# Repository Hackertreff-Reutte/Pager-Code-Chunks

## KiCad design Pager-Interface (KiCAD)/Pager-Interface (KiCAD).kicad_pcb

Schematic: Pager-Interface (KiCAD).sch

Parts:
H1, H2, H3: M3; MountingHole_3.2mm_M3_DIN965_Pad_TopBottom
J1: VSPI; PinHeader_1x06_P2.54mm_Vertical
J2: HSPI; PinHeader_1x06_P2.54mm_Vertical
J3: Serial; PinHeader_1x04_P2.54mm_Vertical
J4: Serial2; PinHeader_1x04_P2.54mm_Vertical
J5: SMA ANT; SMA_Molex_73251-2120_EdgeMount_Horizontal
J6: Ext Power; PinHeader_1x02_P2.54mm_Vertical
J7: Debug SI4432; PinHeader_1x05_P2.54mm_Vertical
J8: Power; PinHeader_1x02_P2.54mm_Vertical
U1: ESP32_NodeMCU
U2: SI4432-Module

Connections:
+3V3: J1.1, J2.1, J3.1, J4.1, J8.1, U1.15, U2.5
/HSPI_CLK: J2.4, U1.20
/HSPI_CS: J2.5, U1.13
/HSPI_MISO: J2.3, U1.19
/HSPI_MOSI: J2.2, U1.18
/RSSI: J7.3, U1.25, U2.4
/RX0: J3.3, U1.4
/RX2: J4.3, U1.10
/RX_Clock: J7.2, U1.26, U2.3
/RX_Data: J7.1, U1.27, U2.2
/SDN: U1.11, U2.11
/TX0: J3.2, U1.3
/TX2: J4.2, U1.9
/VIN: J6.1, U1.16
/VSPI_CLK: J1.4, U1.7, U2.8
/VSPI_CS: J1.5, U1.8, U2.9
/VSPI_MISO: J1.3, U1.6, U2.6
/VSPI_MOSI: J1.2, U1.1, U2.7
/nIRQ: J7.4, U1.12, U2.10
GND: H1.1, H2.1, H3.1, J1.6, J2.6, J3.4, J4.4, J5.2 (Ext), J6.2, J7.5, J8.2, U1.14, U1.17, U2.1, U2.12, U2.14
unnamed: J5.1 (In), U2.13

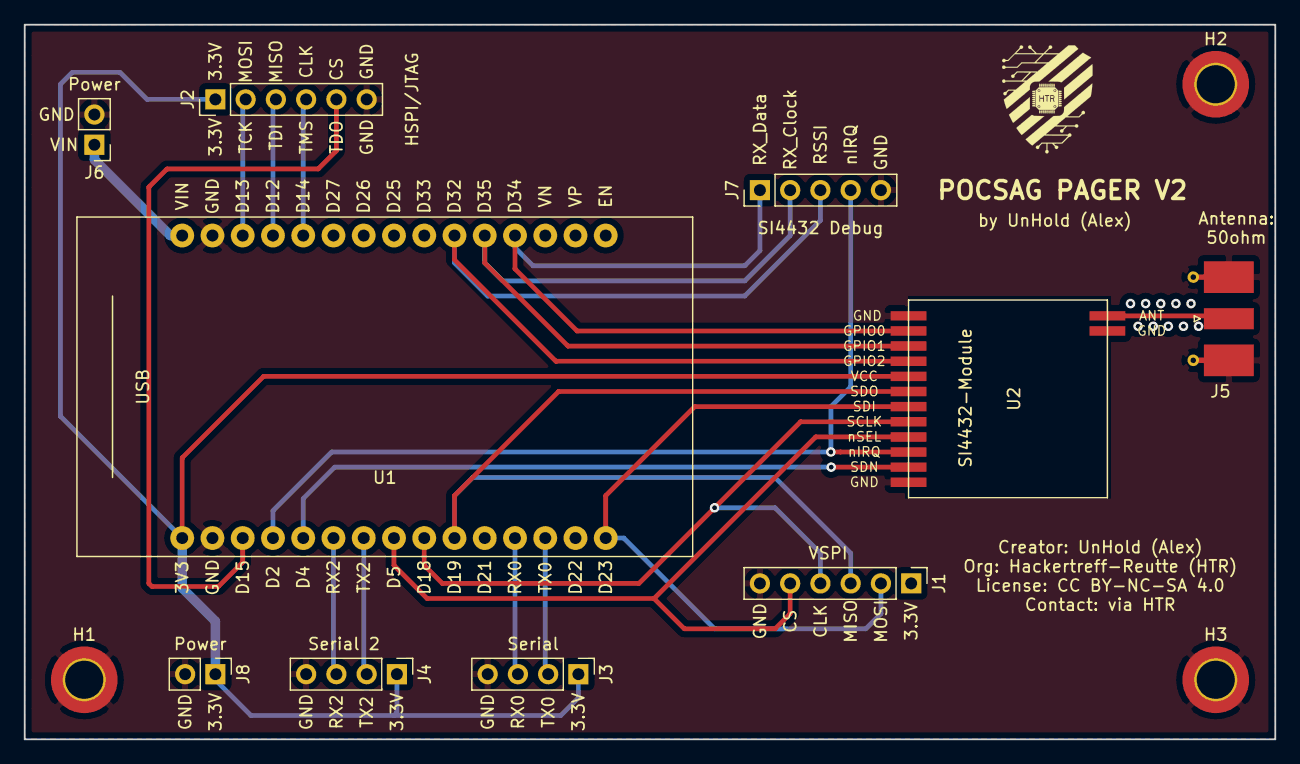
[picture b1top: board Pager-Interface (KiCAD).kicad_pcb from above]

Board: 2 copper layers, 105.0 x 60.0 mm, 13 parts (0 on the bottom side), 21 nets.

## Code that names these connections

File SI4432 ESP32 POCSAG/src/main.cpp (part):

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#include <math.h>
#include <signal.h>

#define HSPI_MISO   12
#define HSPI_MOSI   13
#define HSPI_SCLK   14
#define HSPI_SS     15

#define SDN 16


#define BUFFER_SIZE 1000
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double MODEM_DEVIATION = DEVIATION * 4;

#define INTERRUPT_PIN 5
#define RX_CLOCK_PIN 18
#define RX_DATA_PIN 19
#define RSSI_PIN 21

#define RSSI_RELATIVE_NO_SIGNAL_INDICATOR 0.9

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    return;
  }

  if(digitalRead(RX_CLOCK_PIN) == LOW){
    return;
  }

  tx_buf[si4432_count] |= digitalRead(RX_DATA_PIN) << (7 - si4432_count_shift);

  si4432_count_shift = (si4432_count_shift + 1) % 8;

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
      si4432_count = 0;
      tx_buf[0] = 0;
      attachInterrupt(RX_CLOCK_PIN, si4432_rx_clock_isr, RISING);
      attachInterrupt(RSSI_PIN, si4432_rssi_isr, FALLING);
    }
}

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  setModulationDataSource(SOURCE_DIRECT_SPI);
  setDirectClockSource(NO_TX_DATA_CLK);

  pinMode(RX_CLOCK_PIN, INPUT);
  pinMode(RX_DATA_PIN, INPUT);
  pinMode(INTERRUPT_PIN, INPUT);
  pinMode(RSSI_PIN, INPUT);

  write(0x06, 0b01000000); // disable interrupt (only Preamble interrupt)

  enableRXOutputPins();
  write(0x0D, 0b11100); //RSSI clear channel indicator on GPIO 2

  //register interrupt
  attachInterrupt(INTERRUPT_PIN, si4432_ISR, FALLING);
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  
  //this reset is important because otherwise spi might not be working on the
  //si4432
  pinMode(SDN, OUTPUT);
  digitalWrite(SDN, HIGH);
  delay(500);
  digitalWrite(SDN, LOW);
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  if(si4432_active_receive >= 1){
    if(si4432_active_receive >= 2){
      si4432_active_receive = 0;
      detachInterrupt(RX_CLOCK_PIN);
      detachInterrupt(RSSI_PIN);
      setIDLEMode();

      //send the data
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
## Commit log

2019-11-05 add bch code generator (proof of concept)
2019-11-06 Java program that can generate digitale audio signale (used for the generation of pocsag signals for a radio to transmit)
2019-11-07 added single bit and dual bit code correction
2021-02-16 added code chunks to help with the programming and debugging of the si4432
2021-02-16 renamed file to full name
2021-02-16 added esp32 example code on how to use the si4432 chip for pocsag RX and TX
2021-02-16 removed some duplicated files and fixed the name of a file
2021-02-18 added pocsag RX and TX support via UART
2021-02-20 added basic encoder and decoder + uart conrtol of si4432 + esp32
2021-02-20 fixed transmission size (was too small)
2021-02-21 added python file to fully control the esp32 and the si4432 (send and receive pocsag messages)
2021-02-21 added more functions and fixed a bug where the interrupt triggert incorrectly
2021-02-21 fixed bug where the program crashed when it has too few bits
2021-02-21 added a few more functions
2021-02-21 added option to change the deviation of the modem band width (fixes reception problems)
2021-02-21 added gitingore 4 vscode
2021-02-21 added .vscode to git ignore
2021-02-21 added more gitignore files
2021-02-21 added readme for fsk gnu radio demodulator
2021-02-21 added readme that shortly explains what the script does
2021-02-21 added simple readme for the encoder
2021-02-24 added basic schmematic for connecting the esp32 to an usb programmer
2021-02-24 added si4432 symbol + added and connected si4432 in schematic
2021-02-24 change caps
2021-02-24 Assigned footprint (missing SI4432 module)
2021-02-24 assigned footprints v2
2021-02-24 added footprint for si4432 module + created pcb
2021-02-25 changed part numbers -> cp2102 to gqfn28 footprint + created outputfile for jlcpcb + some more silk text
2021-03-04 Added Readme for the java code
2021-03-04 Added a small readme for the gnu radio demodulator
2021-03-04 rearanged components for better visibility
2021-03-04 removed files that are now in the gitignore and added gitignore
2021-03-04 added function to set gpio pins (si4432)
2021-03-27 Changed the PCB to use the NodeMCU, because it is just a prototype and won't be used in the future
2021-03-27 Added 3D models to the PCB

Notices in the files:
Pager-Interface (KiCAD)/Pager-Interface (KiCAD).kicad_pcb:
License: CC BY-NC-SA 4.0
